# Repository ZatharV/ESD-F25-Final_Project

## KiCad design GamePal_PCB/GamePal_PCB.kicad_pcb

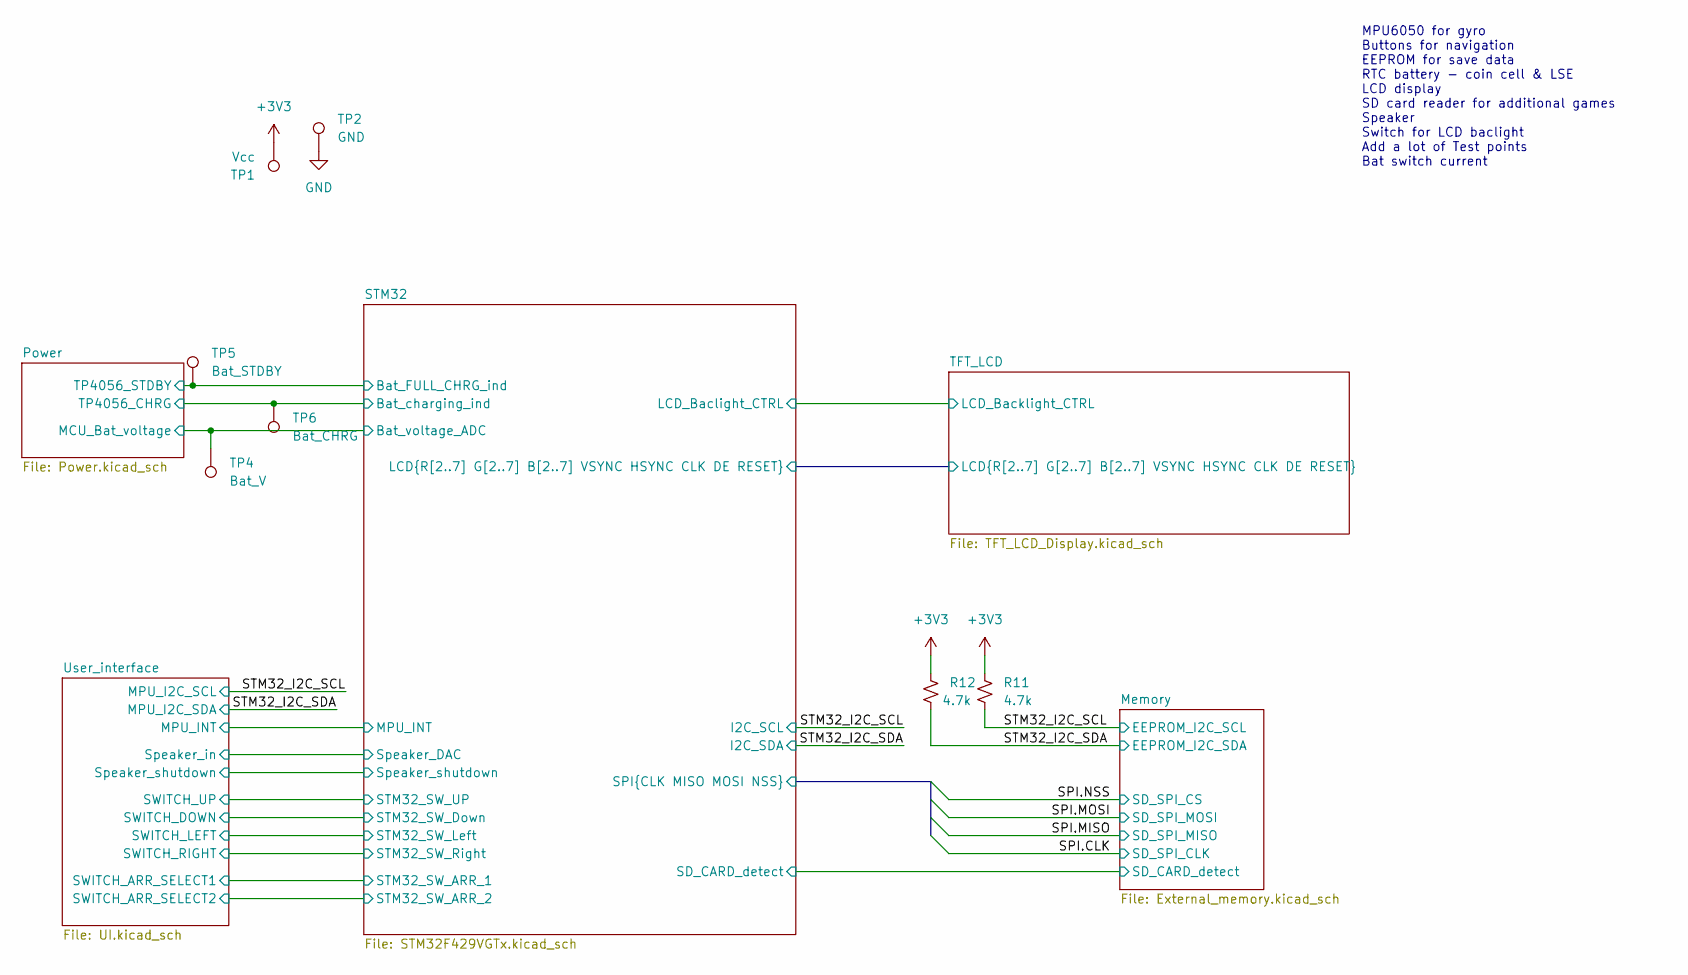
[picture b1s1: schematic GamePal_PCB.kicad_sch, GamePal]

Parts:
R11, R12: 4.7k; R_0603_1608Metric_Pad0.98x0.95mm_HandSolder
TP1: Vcc; TestPoint_Pad_1.5x1.5mm
TP2: GND; TestPoint_Pad_1.5x1.5mm
TP4: Bat_V; TestPoint_Pad_1.5x1.5mm
TP5: Bat_STDBY; TestPoint_Pad_1.5x1.5mm
TP6: Bat_CHRG; TestPoint_Pad_1.5x1.5mm

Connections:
+3V3: R11.1, R12.1, TP1.1; also elsewhere on the board
/Power/MCU_Bat_voltage: TP4.1; also elsewhere on the board
/Power/TP4056_CHRG: TP6.1; also elsewhere on the board
/Power/TP4056_STDBY: TP5.1; also elsewhere on the board
/STM32_I2C_SCL: R11.2; also elsewhere on the board
/STM32_I2C_SDA: R12.2; also elsewhere on the board
GND: TP2.1; also elsewhere on the board

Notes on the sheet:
MPU6050 for gyro Buttons for navigation EEPROM for save data RTC battery - coin cell & LSE LCD display SD card reader for additional games Speaker Switch for LCD baclight Add a lot of Test points Bat switch current

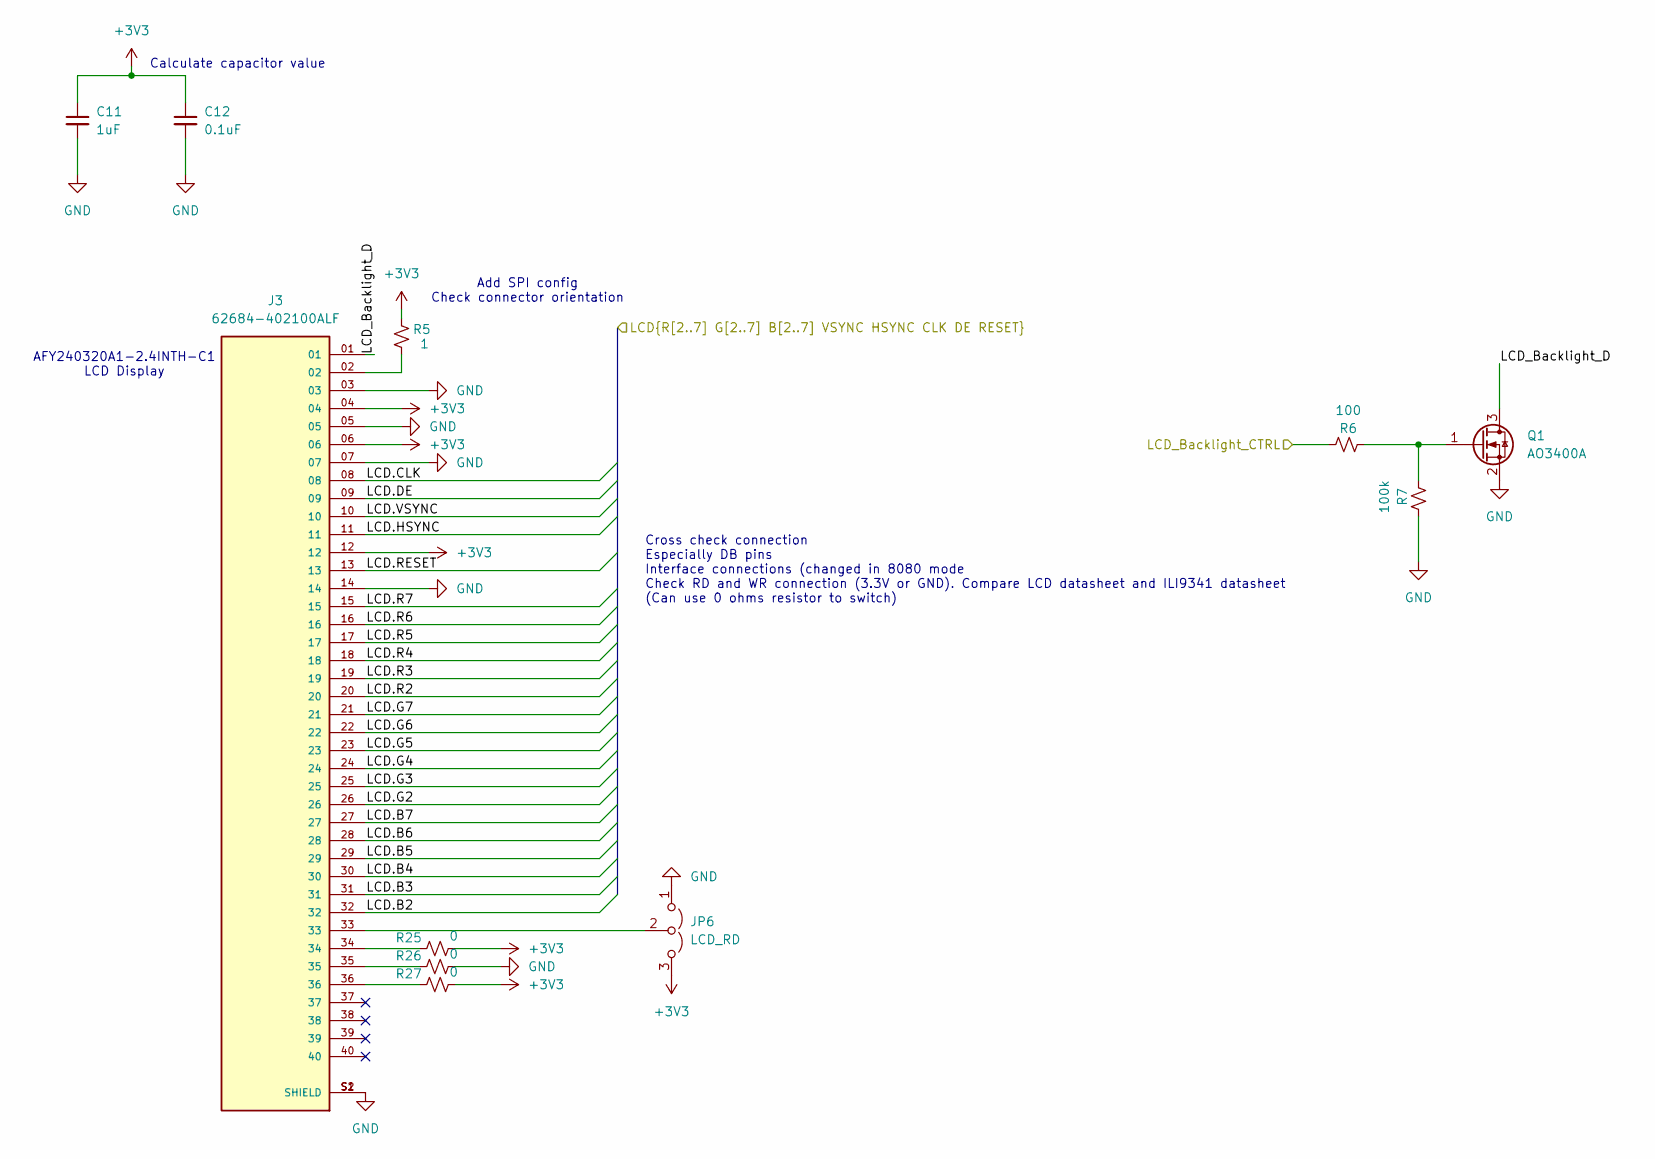
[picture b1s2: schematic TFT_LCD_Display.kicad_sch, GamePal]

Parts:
C11: 1uF; C_0603_1608Metric_Pad1.08x0.95mm_HandSolder
C12: 0.1uF; C_0603_1608Metric_Pad1.08x0.95mm_HandSolder
J3: 62684-402100ALF; AMPHENOL_62684-402100ALF; PARTREV AK
JP6: LCD_RD; SolderJumper-3_P1.3mm_Open_Pad1.0x1.5mm
Q1: AO3400A; TSOT-23
R5: 1; R_0603_1608Metric_Pad0.98x0.95mm_HandSolder
R6: 100; R_0603_1608Metric_Pad0.98x0.95mm_HandSolder
R7: 100k; R_0603_1608Metric_Pad0.98x0.95mm_HandSolder
R25, R26, R27: 0; R_0603_1608Metric_Pad0.98x0.95mm_HandSolder

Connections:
+3V3: C11.1, C12.1, J3.04, J3.06, J3.12, JP6.3 (B), R5.1, R25.2, R27.2; also elsewhere on the board
/STM32/LCD.B2: J3.32; also elsewhere on the board
/STM32/LCD.B3: J3.31; also elsewhere on the board
/STM32/LCD.B4: J3.30; also elsewhere on the board
/STM32/LCD.B5: J3.29; also elsewhere on the board
/STM32/LCD.B6: J3.28; also elsewhere on the board
/STM32/LCD.B7: J3.27; also elsewhere on the board
/STM32/LCD.CLK: J3.08; also elsewhere on the board
/STM32/LCD.DE: J3.09; also elsewhere on the board
/STM32/LCD.G2: J3.26; also elsewhere on the board
/STM32/LCD.G3: J3.25; also elsewhere on the board
/STM32/LCD.G4: J3.24; also elsewhere on the board
/STM32/LCD.G5: J3.23; also elsewhere on the board
/STM32/LCD.G6: J3.22; also elsewhere on the board
/STM32/LCD.G7: J3.21; also elsewhere on the board
/STM32/LCD.HSYNC: J3.11; also elsewhere on the board
/STM32/LCD.R2: J3.20; also elsewhere on the board
/STM32/LCD.R3: J3.19; also elsewhere on the board
/STM32/LCD.R4: J3.18; also elsewhere on the board
/STM32/LCD.R5: J3.17; also elsewhere on the board
/STM32/LCD.R6: J3.16; also elsewhere on the board
/STM32/LCD.R7: J3.15; also elsewhere on the board
/STM32/LCD.RESET: J3.13; also elsewhere on the board
/STM32/LCD.VSYNC: J3.10; also elsewhere on the board
/STM32/LCD_Baclight_CTRL: R6.1; also elsewhere on the board
/TFT_LCD/LCD_Backlight_D: J3.01, Q1.3 (D)
GND: C11.2, C12.2, J3.03, J3.05, J3.07, J3.14, J3.S1 (SHIELD), J3.S2 (SHIELD), JP6.1 (A), Q1.2 (S), R7.1, R26.2; also elsewhere on the board
unnamed: J3.02, R5.2
unnamed: J3.34, R25.1
unnamed: J3.35, R26.1
unnamed: J3.36, R27.1
unnamed: J3.33, JP6.2 (C)
unnamed: Q1.1 (G), R6.2, R7.2

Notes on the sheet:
AFY240320A1-2.4INTH-C1 LCD Display
Cross check connection Especially DB pins Interface connections (changed in 8080 mode Check RD and WR connection (3.3V or GND). Compare LCD datasheet and ILI9341 datasheet (Can use 0 ohms resistor to switch)
Add SPI config Check connector orientation
Calculate capacitor value

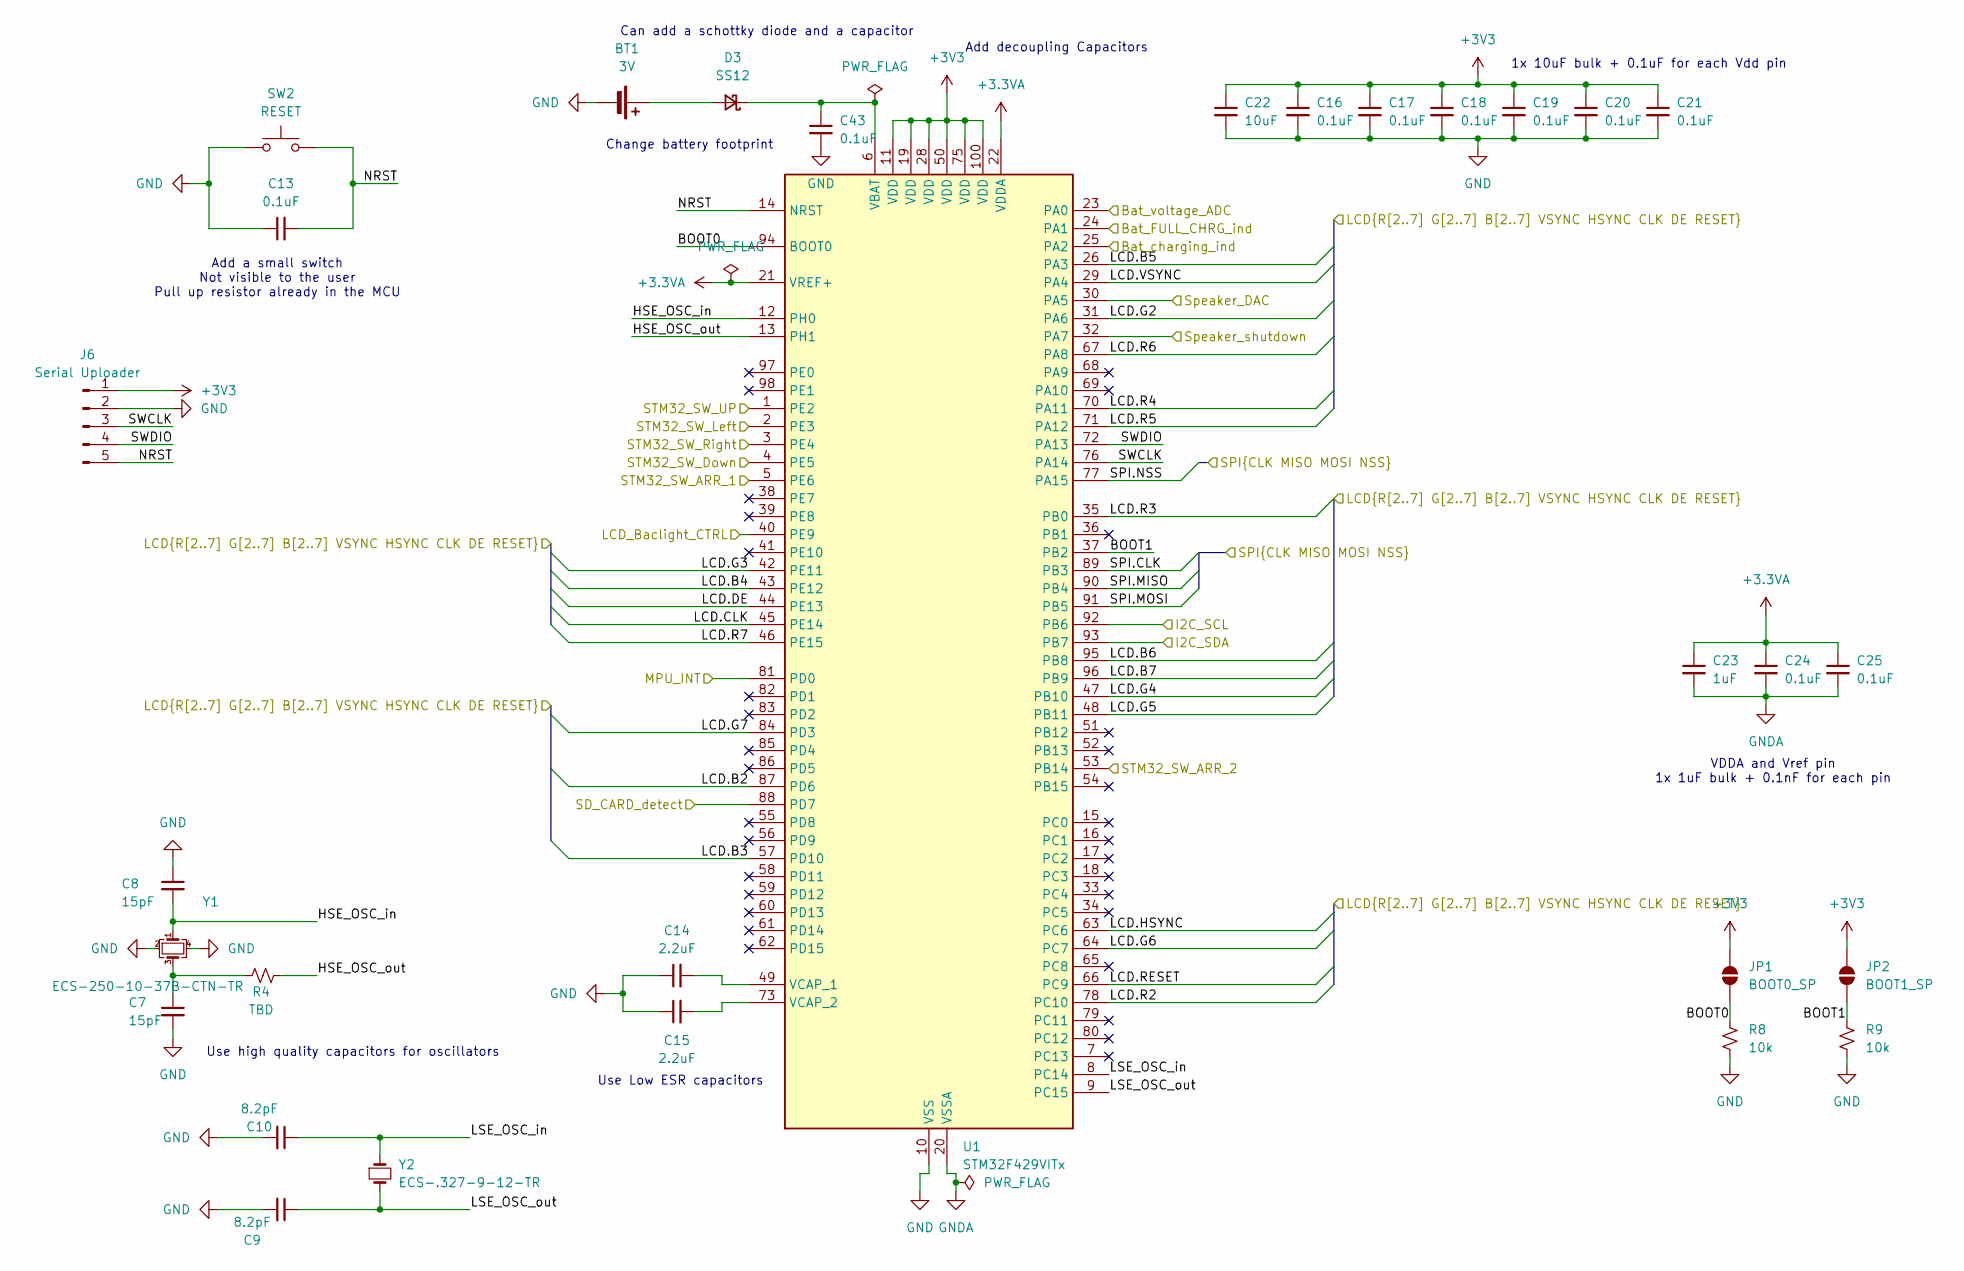
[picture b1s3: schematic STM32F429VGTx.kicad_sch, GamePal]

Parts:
BT1: 3V; BatteryHolder_Seiko_MS621F
C7, C8: 15pF; C_0603_1608Metric_Pad1.08x0.95mm_HandSolder
C9, C10: 8.2pF; C_0603_1608Metric_Pad1.08x0.95mm_HandSolder
C13, C16, C17, C18, C19, C20, C21, C24, C25, C43: 0.1uF; C_0603_1608Metric_Pad1.08x0.95mm_HandSolder
C14, C15: 2.2uF; C_0603_1608Metric_Pad1.08x0.95mm_HandSolder
C22: 10uF; C_0603_1608Metric_Pad1.08x0.95mm_HandSolder
C23: 1uF; C_0603_1608Metric_Pad1.08x0.95mm_HandSolder
D3: SS12; D_SMA
J6: Serial Uploader; PinHeader_1x05_P2.54mm_Vertical_SMD_Pin1Right
JP1: BOOT0_SP; SolderJumper-2_P1.3mm_Open_Pad1.0x1.5mm
JP2: BOOT1_SP; SolderJumper-2_P1.3mm_Open_Pad1.0x1.5mm
R4: TBD; R_0603_1608Metric_Pad0.98x0.95mm_HandSolder
R8, R9: 10k; R_0603_1608Metric_Pad0.98x0.95mm_HandSolder
SW2: RESET; SW_Push_1P1T_NO_CK_KMR2
U1: STM32F429VITx; LQFP-100_14x14mm_P0.5mm
Y1: ECS-250-10-37B-CTN-TR; Crystal_SMD_2016-4Pin_2.0x1.6mm
Y2: ECS-.327-9-12-TR; Crystal_SMD_2012-2Pin_2.0x1.2mm_HandSoldering

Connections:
+3.3VA: C23.1, C24.1, C25.1, U1.21 (VREF+), U1.22 (VDDA); also elsewhere on the board
+3V3: C16.1, C17.1, C18.1, C19.1, C20.1, C21.1, C22.1, J6.1, JP1.2 (B), JP2.2 (B), U1.11 (VDD), U1.19 (VDD), U1.28 (VDD), U1.50 (VDD), U1.75 (VDD), U1.100 (VDD); also elsewhere on the board
/Memory/SD_CARD_detect: U1.88 (PD7); also elsewhere on the board
/Power/MCU_Bat_voltage: U1.23 (PA0); also elsewhere on the board
/Power/TP4056_CHRG: U1.25 (PA2); also elsewhere on the board
/Power/TP4056_STDBY: U1.24 (PA1); also elsewhere on the board
/STM32/BOOT0: JP1.1 (A), R8.1, U1.94 (BOOT0)
/STM32/BOOT1: JP2.1 (A), R9.1, U1.37 (PB2)
/STM32/HSE_OSC_in: C8.2, U1.12 (PH0), Y1.1
/STM32/HSE_OSC_out: R4.1, U1.13 (PH1)
/STM32/LCD.B2: U1.87 (PD6); also elsewhere on the board
/STM32/LCD.B3: U1.57 (PD10); also elsewhere on the board
/STM32/LCD.B4: U1.43 (PE12); also elsewhere on the board
/STM32/LCD.B5: U1.26 (PA3); also elsewhere on the board
/STM32/LCD.B6: U1.95 (PB8); also elsewhere on the board
/STM32/LCD.B7: U1.96 (PB9); also elsewhere on the board
/STM32/LCD.CLK: U1.45 (PE14); also elsewhere on the board
/STM32/LCD.DE: U1.44 (PE13); also elsewhere on the board
/STM32/LCD.G2: U1.31 (PA6); also elsewhere on the board
/STM32/LCD.G3: U1.42 (PE11); also elsewhere on the board
/STM32/LCD.G4: U1.47 (PB10); also elsewhere on the board
/STM32/LCD.G5: U1.48 (PB11); also elsewhere on the board
/STM32/LCD.G6: U1.64 (PC7); also elsewhere on the board
/STM32/LCD.G7: U1.84 (PD3); also elsewhere on the board
/STM32/LCD.HSYNC: U1.63 (PC6); also elsewhere on the board
/STM32/LCD.R2: U1.78 (PC10); also elsewhere on the board
/STM32/LCD.R3: U1.35 (PB0); also elsewhere on the board
/STM32/LCD.R4: U1.70 (PA11); also elsewhere on the board
/STM32/LCD.R5: U1.71 (PA12); also elsewhere on the board
/STM32/LCD.R6: U1.67 (PA8); also elsewhere on the board
/STM32/LCD.R7: U1.46 (PE15); also elsewhere on the board
/STM32/LCD.RESET: U1.66 (PC9); also elsewhere on the board
/STM32/LCD.VSYNC: U1.29 (PA4); also elsewhere on the board
/STM32/LCD_Baclight_CTRL: U1.40 (PE9); also elsewhere on the board
/STM32/LSE_OSC_in: C10.1, U1.8 (PC14), Y2.1
/STM32/LSE_OSC_out: C9.1, U1.9 (PC15), Y2.2
/STM32/MPU_INT: U1.81 (PD0); also elsewhere on the board
/STM32/NRST: C13.2, J6.5, SW2.2, U1.14 (NRST)
/STM32/SPI.CLK: U1.89 (PB3); also elsewhere on the board
/STM32/SPI.MISO: U1.90 (PB4); also elsewhere on the board
/STM32/SPI.MOSI: U1.91 (PB5); also elsewhere on the board
/STM32/SPI.NSS: U1.77 (PA15); also elsewhere on the board
/STM32/STM32_SW_ARR_1: U1.5 (PE6); also elsewhere on the board
/STM32/STM32_SW_ARR_2: U1.53 (PB14); also elsewhere on the board
/STM32/STM32_SW_Down: U1.4 (PE5); also elsewhere on the board
/STM32/STM32_SW_Left: U1.2 (PE3); also elsewhere on the board
/STM32/STM32_SW_Right: U1.3 (PE4); also elsewhere on the board
/STM32/STM32_SW_UP: U1.1 (PE2); also elsewhere on the board
/STM32/SWCLK: J6.3, U1.76 (PA14)
/STM32/SWDIO: J6.4, U1.72 (PA13)
/STM32/Speaker_DAC: U1.30 (PA5); also elsewhere on the board
/STM32/Speaker_shutdown: U1.32 (PA7); also elsewhere on the board
/STM32_I2C_SCL: U1.92 (PB6); also elsewhere on the board
/STM32_I2C_SDA: U1.93 (PB7); also elsewhere on the board
GND: BT1.2 (-), C7.2, C8.1, C9.2, C10.2, C13.1, C14.1, C15.1, C16.2, C17.2, C18.2, C19.2, C20.2, C21.2, C22.2, C43.2, J6.2, R8.2, R9.2, SW2.1, U1.10 (VSS), U1.27 (VSS), U1.74 (VSS), U1.99 (VSS), Y1.2, Y1.4; also elsewhere on the board
GNDA: C23.2, C24.2, C25.2, U1.20 (VSSA); also elsewhere on the board
unnamed: BT1.1 (+), D3.2 (A)
unnamed: C7.1, R4.2, Y1.3
unnamed: C43.1, D3.1 (K), U1.6 (VBAT)
unnamed: C14.2, U1.49 (VCAP_1)
unnamed: C15.2, U1.73 (VCAP_2)

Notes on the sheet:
1x 10uF bulk + 0.1uF for each Vdd pin
Use Low ESR capacitors
VDDA and Vref pin 1x 1uF bulk + 0.1nF for each pin
Can add a schottky diode and a capacitor
Add a small switch Not visible to the user Pull up resistor already in the MCU
Use high quality capacitors for oscillators
Change battery footprint
Add decoupling Capacitors

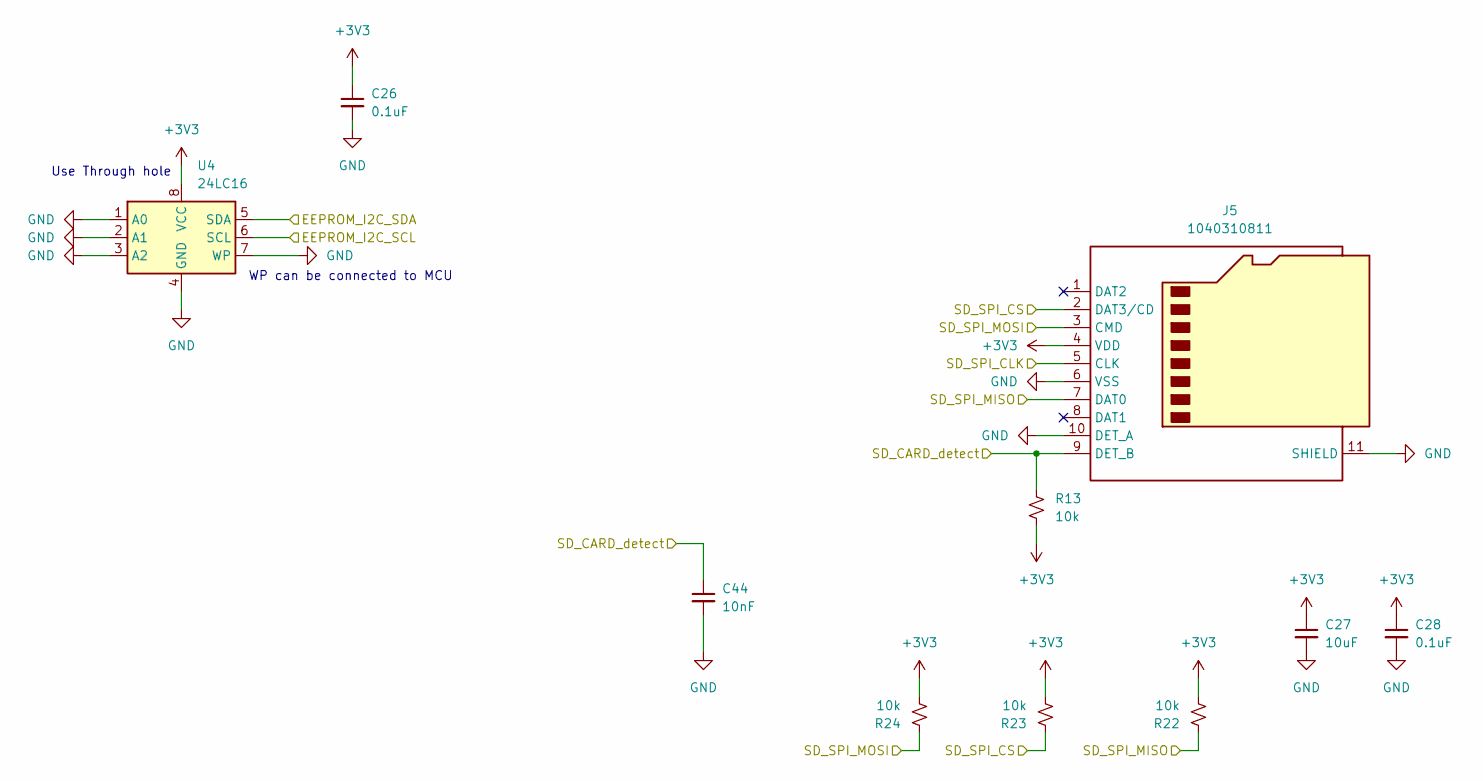
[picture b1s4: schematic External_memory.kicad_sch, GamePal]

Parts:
C26, C28: 0.1uF; C_0603_1608Metric_Pad1.08x0.95mm_HandSolder
C27: 10uF; C_0603_1608Metric_Pad1.08x0.95mm_HandSolder
C44: 10nF; C_0603_1608Metric_Pad1.08x0.95mm_HandSolder
J5: 1040310811; microSD_HC_Molex_104031-0811
R13, R22, R23, R24: 10k; R_0603_1608Metric_Pad0.98x0.95mm_HandSolder
U4: 24LC16; DIP-8_W7.62mm

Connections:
+3V3: C26.1, C27.1, C28.1, J5.4 (VDD), R13.1, R22.1, R23.1, R24.1, U4.8 (VCC); also elsewhere on the board
/Memory/SD_CARD_detect: C44.1, J5.9 (DET_B), R13.2; also elsewhere on the board
/STM32/SPI.CLK: J5.5 (CLK); also elsewhere on the board
/STM32/SPI.MISO: J5.7 (DAT0), R22.2; also elsewhere on the board
/STM32/SPI.MOSI: J5.3 (CMD), R24.2; also elsewhere on the board
/STM32/SPI.NSS: J5.2 (DAT3/CD), R23.2; also elsewhere on the board
/STM32_I2C_SCL: U4.6 (SCL); also elsewhere on the board
/STM32_I2C_SDA: U4.5 (SDA); also elsewhere on the board
GND: C26.2, C27.2, C28.2, C44.2, J5.6 (VSS), J5.10 (DET_A), J5.11 (SHIELD), U4.1 (A0), U4.2 (A1), U4.3 (A2), U4.4 (GND), U4.7 (WP); also elsewhere on the board

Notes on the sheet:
WP can be connected to MCU
Use Through hole

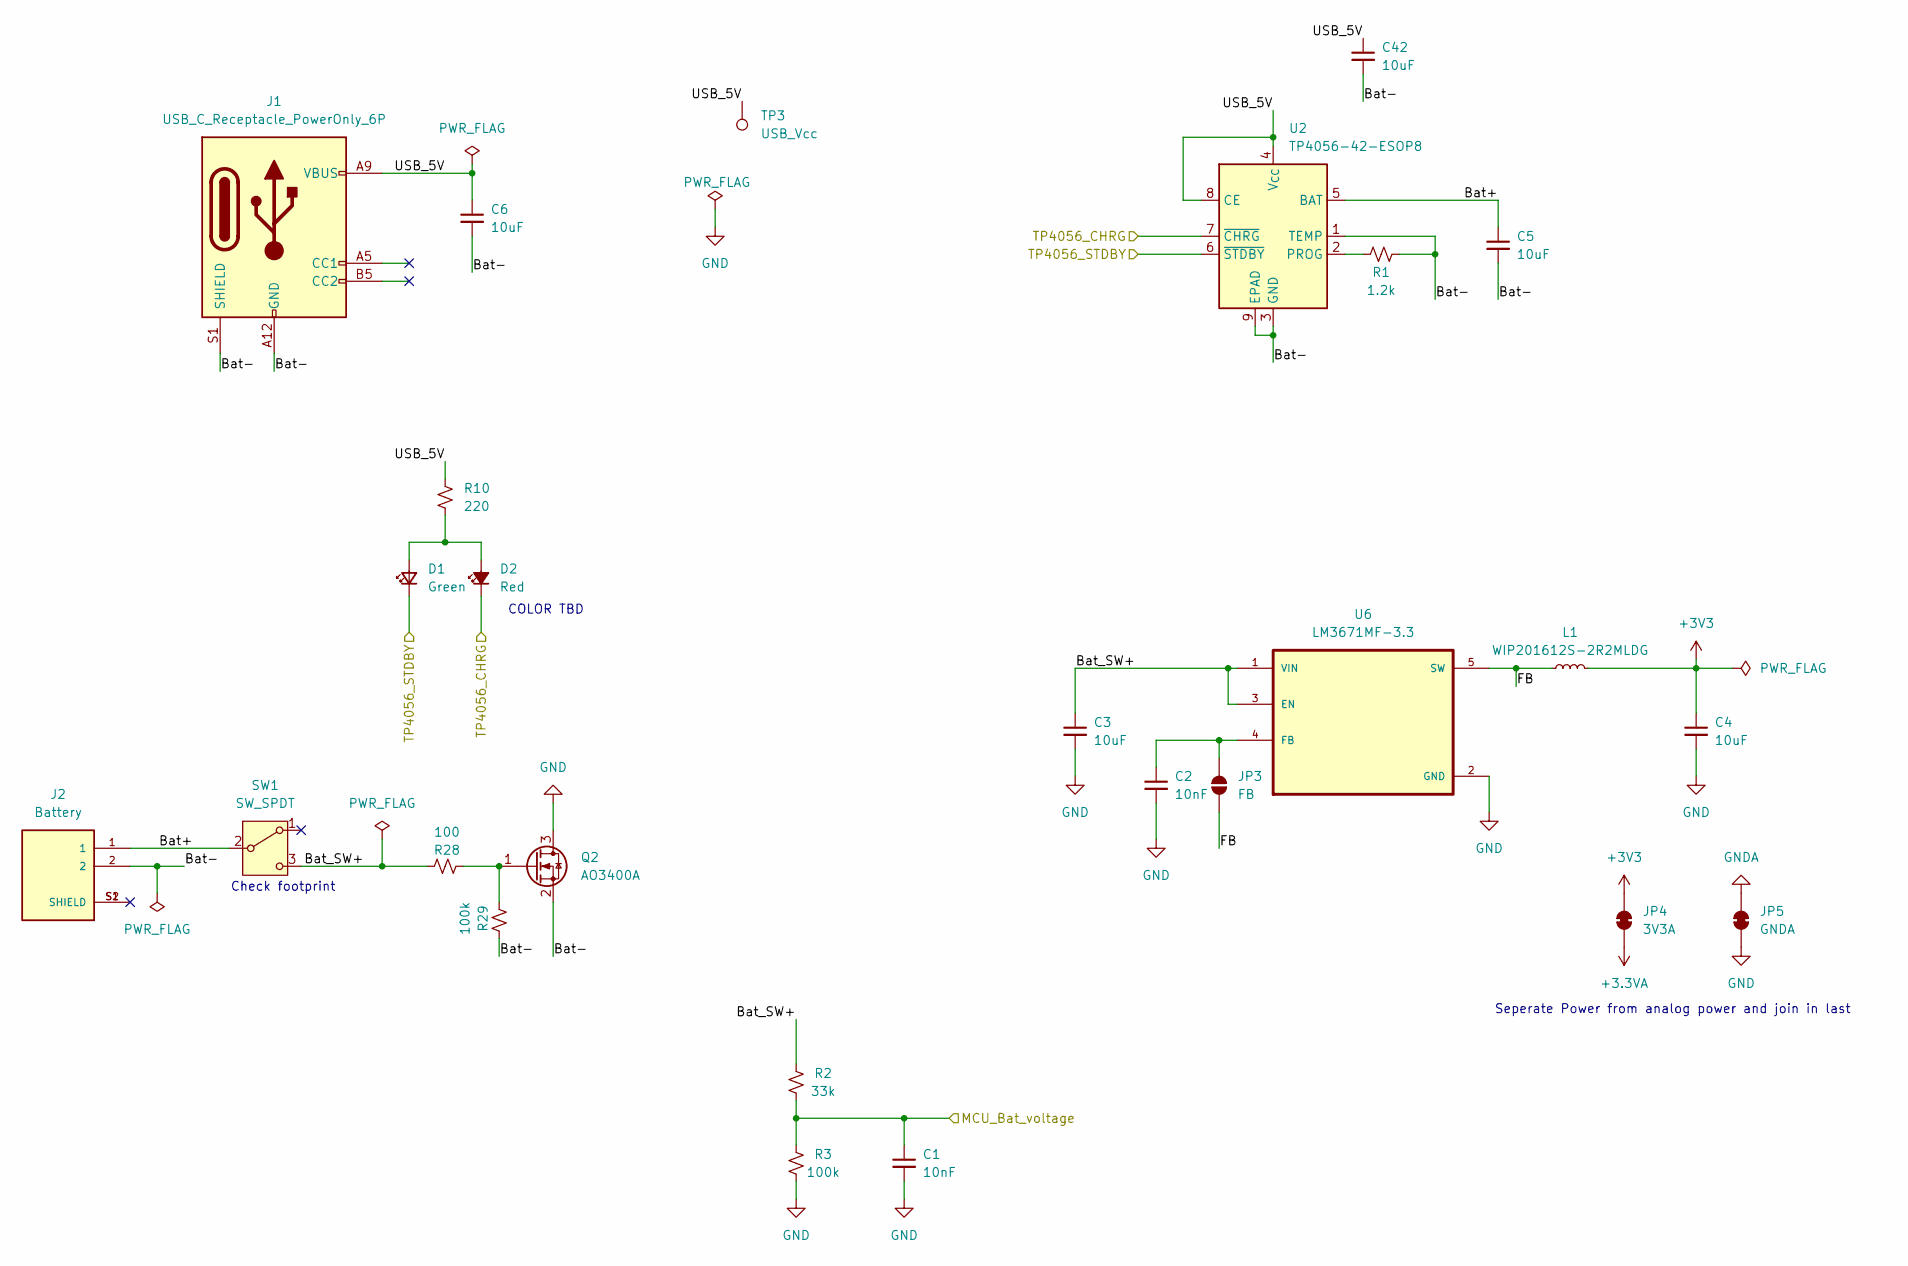
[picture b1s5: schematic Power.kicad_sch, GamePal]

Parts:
C1, C2: 10nF; C_0603_1608Metric_Pad1.08x0.95mm_HandSolder
C3, C4, C5, C6, C42: 10uF; C_0603_1608Metric_Pad1.08x0.95mm_HandSolder
D1: Green; LED_0603_1608Metric
D2: Red; LED_0603_1608Metric
J1: USB_C_Receptacle_PowerOnly_6P; USB_C_Receptacle_GCT_USB4125-xx-x_6P_TopMnt_Horizontal
J2: Battery; JST_BM02B-SRSS-TB_LF__SN_; PARTREV N/A
JP3: FB; SolderJumper-2_P1.3mm_Open_Pad1.0x1.5mm
JP4: 3V3A; SolderJumper-2_P1.3mm_Bridged2Bar_Pad1.0x1.5mm
JP5: GNDA; SolderJumper-2_P1.3mm_Bridged2Bar_Pad1.0x1.5mm
L1: WIP201612S-2R2MLDG; L_Murata_DFE201610P
Q2: AO3400A; TSOT-23
R1: 1.2k; R_0603_1608Metric_Pad0.98x0.95mm_HandSolder
R2: 33k; R_0603_1608Metric_Pad0.98x0.95mm_HandSolder
R3, R29: 100k; R_0603_1608Metric_Pad0.98x0.95mm_HandSolder
R10: 220; R_0603_1608Metric_Pad0.98x0.95mm_HandSolder
R28: 100; R_0603_1608Metric_Pad0.98x0.95mm_HandSolder
SW1: SW_SPDT; SW_SPDT_CK_JS102011SAQN
TP3: USB_Vcc; TestPoint_Pad_1.5x1.5mm
U2: TP4056-42-ESOP8; MSOP-8-1EP_3x3mm_P0.65mm_EP1.95x2.15mm
U6: LM3671MF-3.3; SOT-23-5_HandSoldering

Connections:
+3.3VA: JP4.1 (A); also elsewhere on the board
+3V3: C4.1, JP4.2 (B), L1.2; also elsewhere on the board
/Power/Bat+: C5.1, J2.1, SW1.2 (B), U2.5 (BAT)
/Power/Bat-: C5.2, C6.2, C42.2, J1.A12 (GND), J1.B12 (GND), J1.S1 (SHIELD), J2.2, Q2.2 (S), R1.1, R29.1, U2.1 (TEMP), U2.3 (GND), U2.9 (EPAD)
/Power/Bat_SW+: C3.1, R2.1, R28.1, SW1.3 (C), U6.1 (VIN), U6.3 (EN)
/Power/FB: JP3.1 (A), L1.1, U6.5 (SW)
/Power/MCU_Bat_voltage: C1.1, R2.2, R3.1; also elsewhere on the board
/Power/TP4056_CHRG: D2.1 (K), U2.7 (~CHRG); also elsewhere on the board
/Power/TP4056_STDBY: D1.1 (K), U2.6 (~STDBY); also elsewhere on the board
/Power/USB_5V: C6.1, C42.1, J1.A9 (VBUS), J1.B9 (VBUS), R10.1, TP3.1, U2.4 (V_{CC}), U2.8 (CE)
GND: C1.2, C2.2, C3.2, C4.2, JP5.1 (A), Q2.3 (D), R3.2, U6.2 (GND); also elsewhere on the board
GNDA: JP5.2 (B); also elsewhere on the board
unnamed: D1.2 (A), D2.2 (A), R10.2
unnamed: C2.1, JP3.2 (B), U6.4 (FB)
unnamed: Q2.1 (G), R28.2, R29.2
unnamed: R1.2, U2.2 (PROG)

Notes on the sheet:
Seperate Power from analog power and join in last
Check footprint
COLOR TBD

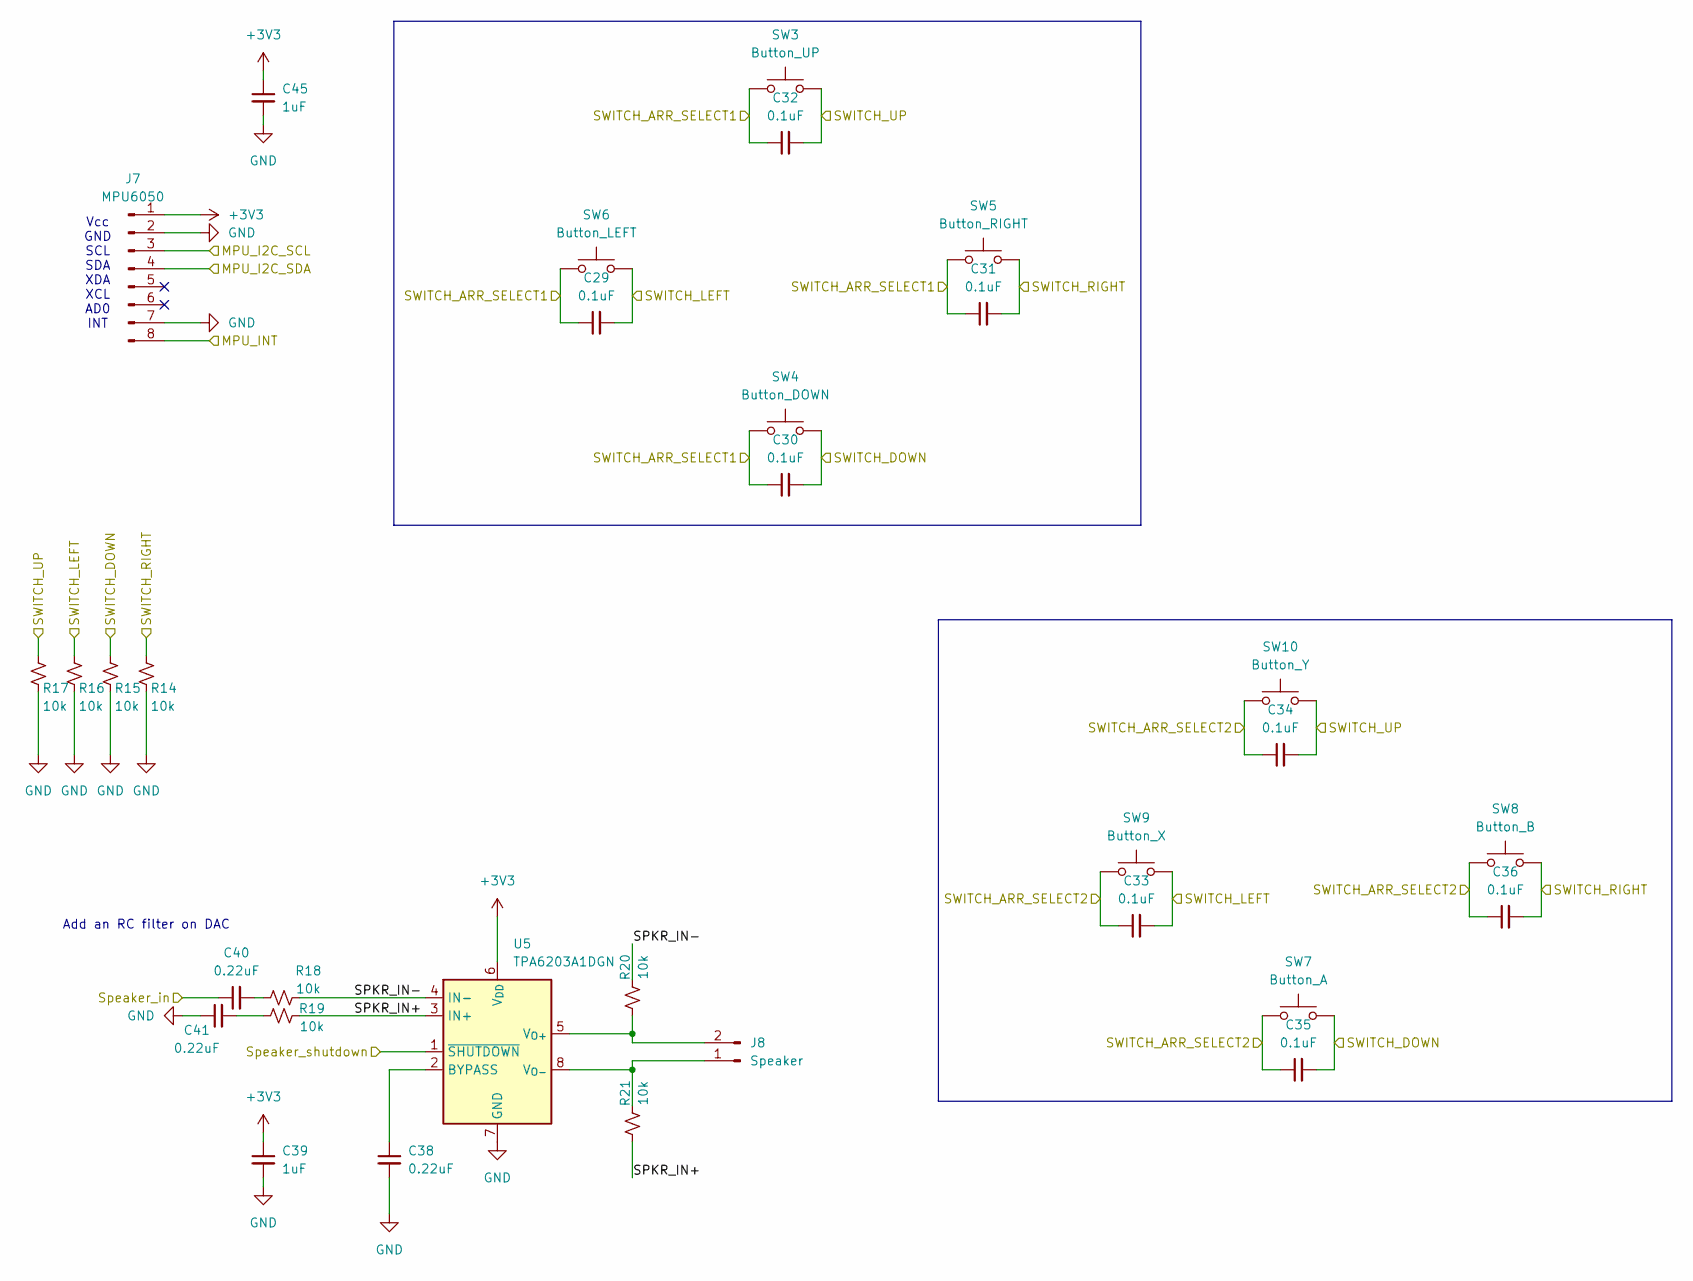
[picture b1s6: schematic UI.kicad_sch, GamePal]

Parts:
C29, C30, C31, C32, C33, C34, C35, C36: 0.1uF; C_0603_1608Metric_Pad1.08x0.95mm_HandSolder
C38, C40, C41: 0.22uF; C_0603_1608Metric_Pad1.08x0.95mm_HandSolder
C39, C45: 1uF; C_0603_1608Metric_Pad1.08x0.95mm_HandSolder
J7: MPU6050; module_mpu6050
J8: Speaker; PinHeader_1x02_P2.54mm_Vertical_SMD_Pin1Left
R14, R15, R16, R17, R18, R19, R20, R21: 10k; R_0603_1608Metric_Pad0.98x0.95mm_HandSolder
SW3: Button_UP; SW_Push_1P1T_NO_E-Switch_TL3301NxxxxxG
SW4: Button_DOWN; SW_Push_1P1T_NO_E-Switch_TL3301NxxxxxG
SW5: Button_RIGHT; SW_Push_1P1T_NO_E-Switch_TL3301NxxxxxG
SW6: Button_LEFT; SW_Push_1P1T_NO_E-Switch_TL3301NxxxxxG
SW7: Button_A; SW_Push_1P1T_NO_E-Switch_TL3301NxxxxxG
SW8: Button_B; SW_Push_1P1T_NO_E-Switch_TL3301NxxxxxG
SW9: Button_X; SW_Push_1P1T_NO_E-Switch_TL3301NxxxxxG
SW10: Button_Y; SW_Push_1P1T_NO_E-Switch_TL3301NxxxxxG
U5: TPA6203A1DGN; MSOP-8-1EP_3x3mm_P0.65mm_EP1.95x2.15mm

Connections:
+3V3: C39.1, C45.1, J7.1, U5.6 (V_{DD}); also elsewhere on the board
/STM32/MPU_INT: J7.8; also elsewhere on the board
/STM32/STM32_SW_ARR_1: C29.1, C30.1, C31.1, C32.1, SW3.1, SW4.1, SW5.1, SW6.1; also elsewhere on the board
/STM32/STM32_SW_ARR_2: C33.1, C34.1, C35.1, C36.1, SW7.1, SW8.1, SW9.1, SW10.1; also elsewhere on the board
/STM32/STM32_SW_Down: C30.2, C35.2, R15.1, SW4.2, SW7.2; also elsewhere on the board
/STM32/STM32_SW_Left: C29.2, C33.2, R16.1, SW6.2, SW9.2; also elsewhere on the board
/STM32/STM32_SW_Right: C31.2, C36.2, R14.1, SW5.2, SW8.2; also elsewhere on the board
/STM32/STM32_SW_UP: C32.2, C34.2, R17.1, SW3.2, SW10.2; also elsewhere on the board
/STM32/Speaker_DAC: C40.1; also elsewhere on the board
/STM32/Speaker_shutdown: U5.1 (~SHUTDOWN); also elsewhere on the board
/STM32_I2C_SCL: J7.3; also elsewhere on the board
/STM32_I2C_SDA: J7.4; also elsewhere on the board
/User_interface/SPKR_IN+: R19.2, R21.1, U5.3 (IN+)
/User_interface/SPKR_IN-: R18.2, R20.2, U5.4 (IN-)
GND: C38.2, C39.2, C41.1, C45.2, J7.2, J7.7, R14.2, R15.2, R16.2, R17.2, U5.7 (GND), U5.9 (GND); also elsewhere on the board
unnamed: C40.2, R18.1
unnamed: C41.2, R19.1
unnamed: J8.1, R21.2, U5.8 (V_{O-})
unnamed: J8.2, R20.1, U5.5 (V_{O+})
unnamed: C38.1, U5.2 (BYPASS)

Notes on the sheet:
Vcc GND SCL SDA XDA XCL AD0 INT
Add an RC filter on DAC

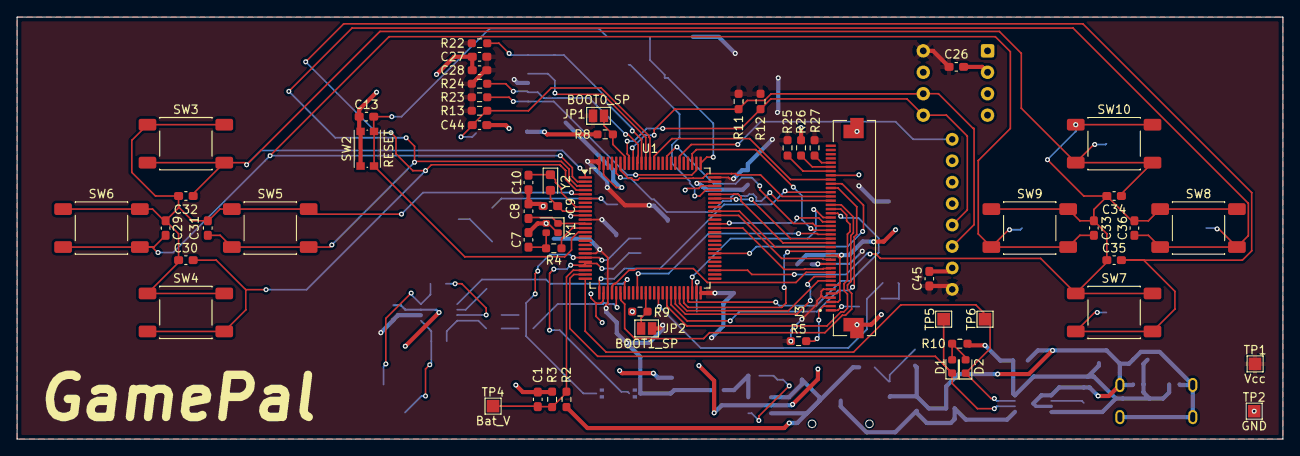
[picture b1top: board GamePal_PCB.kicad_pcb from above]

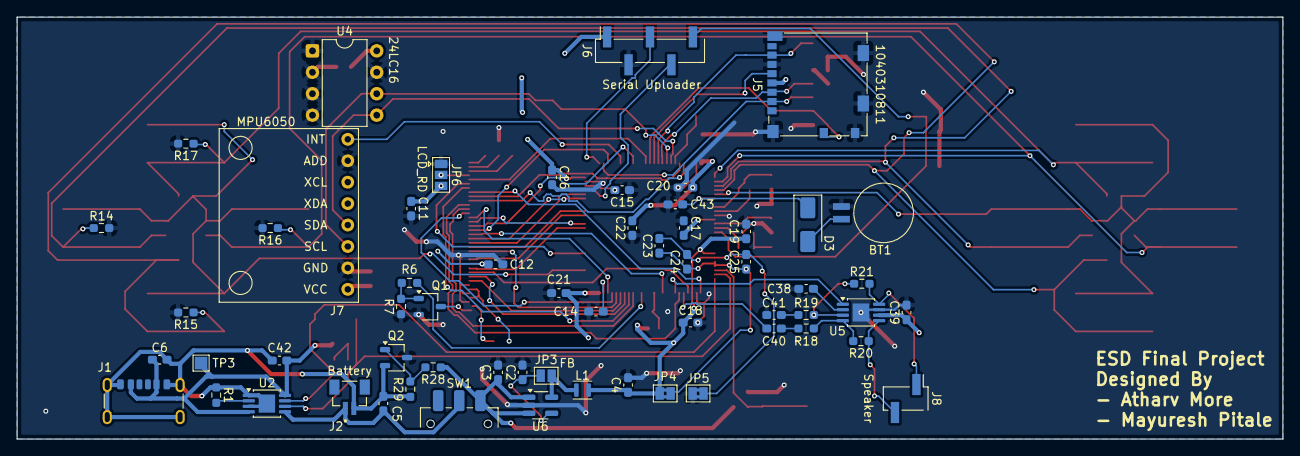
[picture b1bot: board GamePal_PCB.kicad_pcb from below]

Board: 2 copper layers, 150.0 x 50.0 mm, 116 parts (59 on the bottom side), 84 nets.

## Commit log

2025-10-29 PCB init commit
2025-11-03 PCB update
2025-11-09 KICAD PCB LCD connections
2025-11-09 Update PCB
2025-11-10 PCB complete (double check all connections)
2025-11-11 mpu6050 driver
2025-11-18 PCB complete
2025-11-18 PCB Final version
2025-11-18 PCB full and final
2025-11-18 Gerber added
2025-11-18 Final PCB design
2025-11-26 added GPIO and battery test
2025-11-27 DAC test code
2025-11-28 LCD Test code added
2025-11-28 GPIO code added
2025-12-03 Display RGB woring
2025-12-03 Working LCD display
2025-12-04 Project File Update
2025-12-04 T-rex update
2025-12-05 Dino Jump Game update
2025-12-06 Working GamePal
2025-12-09 Final versions of the files
